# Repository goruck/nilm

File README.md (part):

# Energy Management Using Real-Time Non-Intrusive Load Monitoring

## Introduction

The goal of non-intrusive load monitoring (NILM) is to recover the energy consumption of individual appliances from the aggregate mains signal, which is a measure of the total electricity consumption of a building or house. NILM is also known as energy disaggregation and both terms will be used interchangeably throughout.

R. Gopinath, et al., nicely summarizes the rational behind NILM in the paper Energy management using non-intrusive load monitoring techniques — State- of-the-art and future research directions¹:

> In recent years, the development of smart sustainable cities has become the primary focus among urban planners and policy makers to make responsible use of resources, conserve the environment and improve the well-being of the society. Energy management is an integral part of the smart sustainable cities development programme which involves conscious and efficient use of available energy resources towards attaining sustainability and self-reliance on energy systems. Building sector is one of the key sectors that utilize more energy. Therefore, efforts are being made to monitor and manage energy consumption effectively in residential and commercial buildings. In recent years, non-intrusive load monitoring (NILM) technique has become a popular and emerging approach to monitor events (on/off) and energy consumption of appliances/electrical utilities in buildings using single energy meter. The information about the energy consumption at the appliance level would help consumers to understand their appliance usage behavior and take necessary steps for reducing energy consumption.

By using deep learning models trained on publicly available datasets it is now feasible to enable NILM in very cost effective ways by leveraging commodity hardware and open source software. Deploying the trained models at the edge of the power grid, i.e. the building level, results in additional cost savings since it obviates the need for always connected internet cloud services which can be expensive at scale and running the algorithms in real-time provides for low latency operation.

This Project will show you how NILM works by taking you through the steps I used to implement a prototype system at my house.

## Architecture

The following first two diagrams illustrate the NILM concept and process steps at a high level. The last diagram shows my prototype system which is based on these concepts and is implemented using Arduino- and Raspberry Pi-based compute.

")

")

## NILM Algorithm Selection and Models

### Algorithm Selection

Energy disaggregation is a highly underdetermined and a single-channel Blind Source Separation (BSS) problem² which makes it difficult to obtain accurate predictions. Let $M$ be the number of household appliances and $i$ be the index referring to the $i$-th appliance. The aggregate power consumption $x$ at a given time $t$ is the sum of the power consumption of all appliances $M$, denoted by $y_i\forall{i=1,...,M}$. Therefore, the total power consumption $x$ at a given time $t$ can expressed by the equation below.

$$
x(t)=\sum_{i=1}^{M} y_i(t) + \epsilon_{\text{noise}}(t)
$$

(1)

Where $\epsilon_{noise}$ is a noise term. The goal of this project is to solve the inverse problem and estimate the appliance power consumption $y_i$, given the aggregate power signal $x$, and to do so in a manner suitable for deployment at the edge. 

Past approaches have included factorial hidden Markov models (FHMM)¹ and various event-based methods with some success⁶. You can also solve the single-channel BSS problem can by using sequence-to-sequence (seq2seq) learning with neural networks, and it can applied to the NILM problem using transformers, convolutional and recurrent neural networks³. Seq2seq learning involves training a neural network to map between an input time series, such as the aggregate power readings the case of NILM, and a output sequence, such as the estimated energy consumption of a single appliance. A sliding input window is typically used to training the network which generates a corresponding window of the output. This method produces multiple predictions for each appliance in the output so an average of the predictions is used for the final result. Some of the predictions will be more accurate than others, especially those near the midpoint of the input sliding window. The averaging will tend to lower the overall accuracy of the predictions.

Some of the disadvantages of of seq2seq leaning can mitigated by sequence-to-point learning (seq2point) for single-channel BSS⁴. You also use a sliding input signal window in this approach, however the network is trained to predict the output signal only at the midpoint of the window which makes the prediction problem easier on the network, leading to more accurate results.

I selected the seq2point learning approach for my prototype system and my implementation was inspired and guided by work described by Michele D'Incecco, Stefano Squartini and Mingjun Zhong⁵. I developed a variety of seq2point learning models using Tensorflow as shown in the Python module [define_models.py](./ml/define_models.py) but focussed my work on the models `transformer` and `cnn`.

### Neural Network Models

The ```cnn``` model is depicted below for an input sequence length of 599 samples. The model generally follows traditional cnn concepts from vision use cases where several convolutional layers are used to extract features from the input power sequence at gradually finer details as the input traverses through the network. These features are the on-off patterns of the appliances as well as their power consumption levels. Max pooling is used to manage the complexity of the model after each convolutional layer. Finally, dense layers are used to output the final single point power consumption estimate for the window which is de-normalized before using in downstream processing. There are about 40 million parameters in this model using the default values.

The ```transformer``` model is depicted below for an input sequence length of 599 samples where the transformer block is a Bert-style encoder. The input sequence is first passed through a convolutional layer to expand it into a latent space which is analogous to the feature extraction in the cnn model case. These features are pooled and L2 normalized to reduce model complexity and to mitigate the effects of outliers. Next, the sequence features are processed by a Bert-style transformer lineup which includes positional embedding and transformer blocks that applies importance weighting. The output of the encoder is decoded by several layers which are comprised of relative position embedding which applies symmetric weights around the mid-point of the signal, average pooling which reduces the sequence to a single value per feature and then finally dense layers that output the final single point estimated power value for the window which again is de-normalized for downstream processing. There are about six million parameters in this model using the default values.

The Bert-style transformer encoder is depicted below.

## NILM Datasets

There are a number of large-scale publicly available datasets specifically designed to address the NILM problem which were captured in household buildings from various countries. The table⁷ below shows several of the most widely used.

")

The datasets generally include many 10’s of millions of active power, reactive power, current, and voltage samples but with different sampling frequencies which requires you to pre-process the data before use. Most NILM algorithms utilize only real (aka active or true) power data. Five appliances are usually considered for energy disaggregation research which are kettle, microwave, fridge, dish washer and washing machine. These are the appliances I considered for my prototype and following the work of Michele DIncecco, et al.⁵, I mainly focused on the REFIT⁸ dataset but will eventually include UK-DALE and REDD.

Note that these datasets are typically very imbalanced because the majority of the time an appliance is in the off state. 

## Model Training and Results

I used TensorFlow to train and test the model. All code associated with this section can be found on the Machine Learning section of the project’s GitHub, NILM⁹. The seq2point learning models for the appliances were trained individually on z-score standardized REFIT data or normalized to $[0, P_m]$, where $P_m$ is the maximum power consumption of an appliance in its active state. Using normalized data tended to give the best model performance so it is used by default.

I used the following metrics to evaluate the model’s performance. You can view the code that calculates these metrics [here](./ml/nilm_metric.py).

* Mean absolute error ($MAE$), which evaluates the absolute difference between the prediction and the ground truth power at every time point and calculates the mean value, as defined by the equation below.

$$
\mathrm{MAE}=\frac{1}{N}\sum_{i=1}^{N}\lvert \hat{x}_i - x_i\rvert
$$

(2)

* Normalized signal aggregate error ($SAE$), which indicates the relative error of the total energy. Denote $r$ as the total energy consumption of the appliance and $\hat{r}$ as the predicted total energy, then SAE is defined per the equation below.

$$
\mathrm{SAE}=\frac{\lvert \hat{r} - r\rvert}{r}
$$

(3)

* Energy per Day ($EpD$) which measures the predicted energy used in a day, useful when the household users are interested in the total energy consumed in a period. Denote $D$ as the total number of days and $e=\sum_{t}e_t$ as the appliance energy consumed in a day, then EpD is defined per the equation below.

$$
\mathrm{EpD}=\frac{1}{D}\sum_{n=1}^{D} e_n
$$

(4)

* Normalized disaggregation error ($NDE$) which measures the normalized error of the squared difference between the prediction and the ground truth power of the appliances, as defined by the equation below.

$$
\mathrm{NDE}=\frac{\sum_{i,t}\bigl(x_{i,t}-\hat{x}_{i,t}\bigr)^2}{\sum_{i,t} x_{i,t}^2}
$$

(5)

I also used accuracy ($ACC$), F1-score ($F1$) and Matthew’s correlation coefficient ($MCC$) to assess if the model can perform well with the severely imbalanced datasets used to train and test the model. These metrics depend on the on-off status of the device and are computed using the parameters in the [common.py](./ml/common.py) module. $ACC$ is equal to the number of correctly predicted time points over the test dataset. $F1$ and $MCC$ are computed according to the equations below where $TP$ stands for true positives, $TN$ stands for true negatives, $FP$ stands for false positives and $FN$ stands for false negatives.

$$
F_1=\frac{TP}{TP+\frac{1}{2}(FP+FN)}
$$

(6)

$$
\mathrm{MCC}=\frac{TN\cdot TP - FN\cdot FP}{\sqrt{(TP+FP)(TP+FN)(TN+FP)(TN+FN)}}
$$

(7)

$MAE$, $SAE$, $NDE$ and $EpD_e$ (defined as $ 100\% \times (EpD_{predicted} - EpD_{ground\_truth}) / EpD_{ground\_truth}$) reflect the model's ability to correctly predict the appliance energy consumption levels. $F1$ and $MCC$ indicates the model's ability to correctly predict appliance activations using imbalanced classes. $ACC$ is less useful in this application because most of the time the model will correctly predict the appliance is off which dominates the dataset.

A sliding window of 599 samples of the aggregate real power consumption signal is used as inputs to seq2point model and the midpoints of the corresponding windows of the appliances are used as targets. You can see how the samples and targets are generated by an instance of the WindowGenerator Class defined in the [window_generator.py](./ml/window_generator.py) module.

You can see the code I used to train the model in [train.py](./ml/train.py) which uses the `tf.distribute.MirroredStrategy()` distributed training strategy. I used the Keras Adam optimizer and to reduce over-fitting, early stopping is used. The training code can be configured to train the seq2point model from scratch, or given a fitted model, prune it or fine tune it with quantization aware training (QAT), both of which can improve inference performance especially on edge hardware.

The key hyper-parameters for training and the optimizer are summarized below.
* Input Window Size: 599 samples
* Global Batch size: 1024 samples.
* From scratch Learning Rate: 1e-04
* QAT and Prune Learning Rate: 1e-05
* Adam Optimizer: beta_1=0.9, beta_2=0.999, epsilon=1e-08.
* Early Stopping Criteria: 6 epochs.

The loss function<sup>11</sup> shown in the equation below is used to compute training gradients and to evaluate validation loss on a per-batch basis. It consists of a combination of Mean Squared Error, Binary Cross-Entropy and Mean Absolute Error losses, averaged over distributed model replica batches.

$$
L(x,s) = (\hat{x}-x)^{2}
        - [\hat{s}\log s + (1-\hat{s})\log(1-s)]
        + \lambda\,|\hat{x}-x|
$$

for $\hat{x} \in \mathcal{O}$.
(8)

Where $x, \hat{x}\in[0, 1]$ are the ground truth and predicted power usage single point values divided by the maximum power limit per appliance and $s, \hat{s}\in\set{0, 1}$ are the appliance state label and prediction, and $O$ is the set of predictions when either the status label is on or the prediction is incorrect. The hyperparameter $\lambda$ tunes the absolute loss term on an a per-appliance basis. 

You can find the training results for each appliance in the [models](./ml/models/) folder. Typical performance metrics for the `cnn` model are shown in the table below.

|Appliance|$F1\uparrow$|$MCC\uparrow$|$ACC\uparrow$|$MAE$ $(W)$ $\downarrow$|$SAE\downarrow$|$NDE\downarrow$|$EpD_e\thinspace(\%)\downarrow$|
| --- | --- | --- | --- | --- | --- | --- | --- |
|kettle|0.7309|0.7346|0.9960|8.788|0.2284|0.4696|-22.85|
|microwave|0.5671|0.5667|0.9933|7.564|0.0460|0.8845|-4.661|
|fridge|0.7929|0.6942|0.8645|12.33|0.0373|0.4111|3.733|
|dishwasher|0.6069|0.6483|0.9801|5.367|0.0347|0.3742|-3.473|
|washingmachine|0.8478|0.8441|0.9893|14.75|0.2929|0.3470|-29.29|

Typical performance metrics for the `transformer` model are shown in the table below.

|Appliance|$F1\uparrow$|$MCC\uparrow$|$ACC\uparrow$|$MAE$ $(W)$ $\downarrow$|$SAE\downarrow$|$NDE\downarrow$|$EpD_e\thinspace(\%)\downarrow$|
| --- | --- | --- | --- | --- | --- | --- | --- |
|kettle|0.8177|0.8176|0.9967|7.264|0.1348|0.3760|13.48|
|microwave|0.6530|0.6506|0.9952|6.428|0.1454|0.7496|-14.54|
|fridge|0.8138|0.7262|0.8799|11.02|0.0559|0.3743|5.590|
|dishwasher|0.6914|0.7119|0.9873|5.373|0.0690|0.3906|-6.904|
|washingmachine|0.8435|0.8420|0.9886|14.19|0.2440|0.2440|-24.40|

Average metrics across all appliances for both model architectures are compared in the table below.

|Architecture|$\overline{F1}\uparrow$|$\overline{MCC}\uparrow$|$\overline{ACC}\uparrow$|$\overline{MAE}$ $(W)$ $\downarrow$|$\overline{SAE}\downarrow$|$\overline{NDE}\downarrow$|$\overline{\|EpD_e\|}\thinspace(\%)\downarrow$|
| --- | --- | --- | --- | --- | --- | --- | --- |
|```cnn```|0.7161|0.7065|0.9643|9.852|0.1957|0.4528|19.57|
|```transformer```|0.7639|0.7497|0.9695|8.855|0.1298|0.3781|12.98|

You can see that the ```cnn``` and ```transformer``` models have similar performance even though the latter has about six times fewer parameters than the former. However, each ```transformer``` training step takes about seven times longer than ```cnn``` due to the `transformer` model's use of self-attention which has $O(n^2)$ complexity as compared to the `cnn` model's $O(n)$, where $n$ is the input sequence length. On the basis on training (and inference) efficiency, you can see that ```cnn``` is preferable with little loss in model performance.

You can find a variety of performance metrics in the literature to compare these results against, here are two examples. The middle column in the table<sup>5</sup> below shows another cnn-based model's performance. You can see the results of this project compare very favorably. 

The table<sup>12</sup> below shows the results from two transformer-based models (BERT4NILM and ELECTRIcity) and three other architectures. Although the data is incomplete, again this project's transformer-based model results compare favorably. 

## Model Quantization

I performed [Post-training quantization](https://www.tensorflow.org/lite/performance/post_training_quantization) on the ```cnn``` and ```transformer``` models using the [TensorFlow Lite converter API](https://www.tensorflow.org/lite/models/convert/) with various quantization modes to improve inference speed on edge hardware, including the Raspberry Pi and the Google Edge TPU, while mitigating the impact on accuracy. You can see the quantization modes I used in the table below.

|Mode|Description|
| --- | --- |
|convert_only|Convert to tflite but keep all parameters in Float32 (no quantization).|
|w8|Quantize weights from float32 to int8 and biases to int64. Leave activations in Float32.|
|w8_a8_fallback|Same as w8 but quantize activations from float32 to int8. Fallback to float if an operator does not have an integer implementation.|
|w8_a8|Same as w8 but quantize activations from float32 to int8. Enforce full int8 quantization for all operators.|
|w8_a16|Same as w8 but quantize activations to int16.|

The `cnn` model was quantized using all modes to understand the best tradeoff between latency and accuracy. Only the weights for the ```transformer``` model were quantized to int8 using mode `w8`, the activations needed to be kept in Float32 to maintain acceptable accuracy. See [convert_keras_to_tflite.py](./ml/convert_keras_to_tflite.py) for the code that does this quantization which also uses [TensorFlow Lite's quantization debugger](https://www.tensorflow.org/lite/performance/quantization_debugger) to check how well each layer in the model was quantized. I also profiled the converted models using the [TensorFlow Lite Model Benchmark Tool](https://github.com/tensorflow/tensorflow/tree/master/tensorflow/lite/tools/benchmark) to quantify inference latencies.

The quantized inference results are shown in the tables below, where $L_{x86}$ is the average inference latency on a 3.8 GHz x86 machine using eight tflite interpreter threads and $L_{arm}$ is the average inference latency on the ARM aarch-64-based Raspberry Pi 4 using four threads with both computers using the TensorFlow Lite [XNNPACK](https://github.com/google/XNNPACK) CPU delegate. $L_{tpu}$ is the average inference latency on the Google Coral Edge TPU. Model inputs and outputs were keep in float32 to maximize inference speed for the x86- and ARM-based machines but were set to int8 for the edge tpu.

### CNN Model Results and Discussion

The quantized results for the ```cnn``` models are shown in the table below for quantization mode ```w8```.

|Appliance|$F1\uparrow$|$MCC\uparrow$|$ACC\uparrow$|$MAE$ $(W)$ $\downarrow$|$SAE\downarrow$|$NDE\downarrow$|$EpD_e$ ($\%$)|$L_{x86}$ (${\mu}s$)|$L_{arm}$ (${\mu}s$)|
| --- | --- | --- | --- | --- | --- | --- | --- | --- | --- |
|kettle|0.7428|0.7454|0.9966|7.371|0.2013|0.4500|-20.13|743.910|3809.41|
|microwave|0.6400|0.6373|0.9933|7.971|0.1578|0.7194|-15.78|736.549|3586.55|
|fridge|0.6491|0.5040|0.7935|17.78|0.0907|0.7000|-8.971|731.371|3520.54|
|dishwasher|0.5143|0.5787|0.9719|5.3955|0.0569|0.3647|-5.694|742.279|3519.52|
|washingmachine|0.8838|0.8791|0.9919|15.33|0.2930|0.3811|-29.30|751.801|3515.68|

The quantized results for the ```cnn kettle``` model are shown below for the other quantization modes.

|Mode|$F1\uparrow$|$MCC\uparrow$|$ACC\uparrow$|$MAE$ $(W)$ $\downarrow$|$SAE\downarrow$|$NDE\downarrow$|$EpD_e$ ($\%$)|$L_{x86}$ (${\mu}s$)|$L_{arm}$ (${\mu}s$)|$L_{tpu}$ (${\mu}s$)|
| --- | --- | --- | --- | --- | --- | --- | --- | --- | --- | --- |
|convert_only|0.7119|0.7199|0.9964|7.812|0.2862|0.4780|-28.65|309.531|12890.10|NA|
|w8_a8_fallback|0.6584|0.6736|0.9959|8.677|0.3700|0.5448|-36.70|186.483|3435.56|NA|
|w8_a8|0.6584|0.6736|0.9960|8.768|0.3670|0.5447|-36.70|185.403|3258.19|27777.8|
|w8_a16|0.7474|0.7479|0.9966|7.431|0.1531|0.4516|-15.31|5095.38|24065.3|NA|

The quantized results for the ```cnn microwave``` model are shown below for the other quantization modes.

|Mode|$F1\uparrow$|$MCC\uparrow$|$ACC\uparrow$|$MAE$ $(W)$ $\downarrow$|$SAE\downarrow$|$NDE\downarrow$|$EpD_e$ ($\%$)|$L_{x86}$ (${\mu}s$)|$L_{arm}$ (${\mu}s$)|$L_{tpu}$ (${\mu}s$)|
| --- | --- | --- | --- | --- | --- | --- | --- | --- | --- | --- |
|convert_only|0.6410|0.6384|0.9933|7.976|0.1630|0.7195|-18.30|302.750|13055.3|NA|
|w8_a8_fallback|0.6268|0.6238|0.9931|8.006|0.1796|0.7206|-17.96|187.232|3458.30|NA|
|w8_a8|0.6268|0.6238|0.9931|8.005|0.1796|0.7206|-17.96|183.910|3466.65|100000|
|w8_a16|0.6391|0.6365|0.9933|7.968|0.1590|0.7172|-15.89|5100.76|24052.0|NA|

Results for the other appliance models are omitted for brevity but show similar characteristics as a function of quantization mode.

You can see the negative impact of activation quantization but weight quantization, because of regularization effects, has a moderate benefit on some model performance metrics. As expected, the full quantization modes lead to the lowest latencies. Quantizing activations to int16 by the ```w8_a16``` mode results in the highest latencies because only non-optimized reference kernel implementations are presently available in TensorFlow Lite but this scheme leads to the best model metrics given the regularization benefits from weight quantization and better preservation of activation numerics.

You can also see that inference latency of the modes follows ```w8``` ${>}$ ```convert_only``` ${>}$ ```w8_a8``` for the x86 machine but ```convert_only``` ${>}$ ```w8``` ${>}$ ```w8_a8``` for the aarch64 machine, although the variation is larger for x86. To better understand this, I profiled the converted models using the [TFLite Model Benchmark Tool](https://github.com/tensorflow/tensorflow/tree/master/tensorflow/lite/tools/benchmark). A summary of the profiling results for the ```cnn microwave``` model are shown below which are representative of the other models.

#### Model Profiling on x86 (slowest to fastest)
You can see that the Fully Connected and Convolution operations are taking the longest to execute in all cases but are much faster in the fully quantized mode of ```w8_a8```.

| w8 node type                     | count | avg_ms | avg %    | cdf %    | mem KB | times called |
| ----------------------------- | ----- | ------ | -------- | -------- | ------ | ------------ |
| FULLY_CONNECTED               | 2     | 0.397  | 56.5527% | 56.5527% | 0      | 2            |
| CONV_2D                       | 4     | 0.204  | 29.0598% | 85.6125% | 0      | 4            |
| Copy (NC X32)                 | 2     | 0.051  | 7.26496% | 92.8775% | 0      | 9            |
| Max Pooling (NHWC F32)        | 1     | 0.038  | 5.41311% | 98.2906% | 0      | 4            |
| Convolution (NHWC F32) IGEMM  | 1     | 0.012  | 1.7094%  | 100%     | 0      | 1            |
| Fully Connected (NC F32) GEMM | 1     | 0      | 0%       | 100%     | 0      | 1            |
| EXPAND_DIMS                   | 9     | 0      | 0%       | 100%     | 0      | 9            |

| convert_only node type        | count | avg_ms | avg %    | cdf %    | mem KB | times called |
| ----------------------------- | ----- | ------ | -------- | -------- | ------ | ------------ |
| Fully Connected (NC F32) GEMM | 3     | 0.151  | 53.3569% | 53.3569% | 0      | 3            |
| Convolution (NHWC F32) IGEMM  | 1     | 0.062  | 21.9081% | 75.265%  | 0      | 5            |
| Max Pooling (NHWC F32)        | 1     | 0.037  | 13.0742% | 88.3392% | 0      | 4            |
| Copy (NC X32)                 | 1     | 0.033  | 11.6608% | 100%     | 0      | 9            |
| EXPAND_DIMS                   | 9     | 0      | 0%       | 100%     | 0      | 9            |

| w8_a8 node type                     | count | avg_ms | avg %    | cdf %    | mem KB | times called |
| ----------------------------- | ----- | ------ | -------- | -------- | ------ | ------------ |
| Convolution (NHWC QC8) IGEMM  | 1     | 0.061  | 37.1951% | 37.1951% | 0      | 5            |
| Fully Connected (NC QS8) GEMM | 3     | 0.037  | 22.561%  | 59.7561% | 0      | 3            |
| Max Pooling (NHWC S8)         | 1     | 0.034  | 20.7317% | 80.4878% | 0      | 4            |
| Copy (NC X8)                  | 1     | 0.032  | 19.5122% | 100%     | 0      | 9            |
| EXPAND_DIMS                   | 9     | 0      | 0%       | 100%     | 0      | 9            |
| Convert (NC QS8 F32)          | 1     | 0      | 0%       | 100%     | 0      | 1            |
| Convert (NC F32 QS8)          | 1     | 0      | 0%       | 100%     | 0      | 1            |

#### Model Profiling on aarch64 (slowest to fastest)
You can see the copy and Max Pooling operations in particular are relatively slower on x86 than on aarch64 which is probably due to memory bandwidth and micro-architecture differences.

| convert_only node type | count | avg_ms | avg %       | cdf %    | mem KB | times called |
| ------------------------------ | ----- | ------ | ----------- | -------- | ------ | ------------ |
| Copy (NC X32)                  | 1     | 34.835 | 30.9136%    | 30.9136% | 0      | 9            |
| Convolution (NHWC F32) IGEMM   | 1     | 32.414 | 28.7651%    | 59.6787% | 0      | 5            |
| Max Pooling (NHWC F32)         | 1     | 23.008 | 20.418%     | 80.0967% | 0      | 4            |
| Fully Connected (NC F32) GEMM  | 3     | 22.425 | 19.9006%    | 99.9973% | 0      | 3            |
| EXPAND_DIMS                    | 9     | 0.003  | 0.00266229% | 100%     | 0      | 9            |

| w8 node type                     | count | avg_ms | avg %       | cdf %    | mem KB | times called |
| ----------------------------- | ----- | ------ | ----------- | -------- | ------ | ------------ |
| Max Pooling (NHWC F32)        | 1     | 42.281 | 46.9085%    | 46.9085% | 0      | 4            |
| CONV_2D                       | 4     | 17.461 | 19.3721%    | 66.2806% | 0      | 4            |
| Copy (NC X32)                 | 2     | 16.877 | 18.7241%    | 85.0047% | 0      | 9            |
| Convolution (NHWC F32) IGEMM  | 1     | 10.658 | 11.8245%    | 96.8292% | 0      | 1            |
| FULLY_CONNECTED               | 2     | 2.847  | 3.1586%     | 99.9878% | 0      | 2            |
| Fully Connected (NC F32) GEMM | 1     | 0.007  | 0.00776613% | 99.9956% | 0      | 1            |
| EXPAND_DIMS                   | 9     | 0.004  | 0.00443779% | 100%     | 0      | 9            |

| w8_a8 node type                     | count | avg_ms | avg %        | cdf %    | mem KB | times called |
| ----------------------------- | ----- | ------ | ------------ | -------- | ------ | ------------ |
| Copy (NC X8)                  | 1     | 34.686 | 30.9647%     | 30.9647% | 0      | 9            |
| Convolution (NHWC QC8) IGEMM  | 1     | 33.259 | 29.6908%     | 60.6554% | 0      | 5            |
| Max Pooling (NHWC S8)         | 1     | 23.922 | 21.3555%     | 82.0109% | 0      | 4            |
| Fully Connected (NC QS8) GEMM | 3     | 20.146 | 17.9846%     | 99.9955% | 0      | 3            |
| EXPAND_DIMS                   | 9     | 0.002  | 0.00178543%  | 99.9973% | 0      | 9            |
| Convert (NC F32 QS8)          | 1     | 0.002  | 0.00178543%  | 99.9991% | 0      | 1            |
| Convert (NC QS8 F32)          | 1     | 0.001  | 0.000892714% | 100%     | 0      | 1            |

#### Quantization Efficacy

The RMSE / scale is close to $1 / sqrt(12)$ (~ 0.289) when quantized distribution is similar to the original float distribution, indicating a well-quantized model. The larger the value is, it's more likely for the layer not being quantized well. The tables below show the RMSE / Scale metric for the ```cnn kettle``` and ```cnn washingmachine``` models and the `Suspected?` column indicates a layer that significantly exceeds 0.289. Other models are omitted for brevity but show similar results. These layers can remain in float to generate a selectively quantized model that increases accuracy at the expense of inference performance but doing so for the ```cnn``` models did not materially improve accuracy. See [Inspecting Quantization Errors with Quantization Debugger](https://www.tensorflow.org/lite/performance/quantization_debugger).

Layer quantization efficacy metrics for the `cnn kettle` model using mode `w8_a8` are shown below.

| layer | op_name | range | rmse/scale | Suspected? |
| ------ | --------------- | --------- | ---------- | --- |
| 0      | EXPAND_DIMS     | 23.929975 | 2.75E-01   |
| 1      | CONV_2D         | 5.518012  | 2.22E-01   |
| 2      | RESHAPE         | 5.518012  | 2.38E-06   |
| 3      | EXPAND_DIMS     | 5.518012  | 2.38E-06   |
| 4      | MAX_POOL_2D     | 5.518012  | 2.42E-06   |
| 5      | RESHAPE         | 5.518012  | 2.42E-06   |
| 6      | EXPAND_DIMS     | 5.518012  | 2.42E-06   |
| 7      | CONV_2D         | 3.494575  | 1.79E-01   |
| 8      | RESHAPE         | 3.494575  | 1.44E-06   |
| 9      | EXPAND_DIMS     | 3.494575  | 1.44E-06   |
| 10     | MAX_POOL_2D     | 3.494575  | 1.49E-06   |
| 11     | RESHAPE         | 3.494575  | 1.49E-06   |
| 12     | EXPAND_DIMS     | 3.494575  | 1.49E-06   |
| 13     | CONV_2D         | 5.910911  | 1.22E-01   |
| 14     | RESHAPE         | 5.910911  | 1.09E-06   |
| 15     | EXPAND_DIMS     | 5.910911  | 1.09E-06   |
| 16     | MAX_POOL_2D     | 5.910911  | 1.18E-06   |
| 17     | RESHAPE         | 5.910911  | 1.18E-06   |
| 18     | EXPAND_DIMS     | 5.910911  | 1.18E-06   |
| 19     | CONV_2D         | 10.82671  | 1.00E-01   |
| 20     | RESHAPE         | 10.82671  | 1.00E-06   |
| 21     | EXPAND_DIMS     | 10.82671  | 1.00E-06   |
| 22     | MAX_POOL_2D     | 10.82671  | 1.08E-06   |
| 23     | RESHAPE         | 10.82671  | 1.08E-06   |
| 24     | EXPAND_DIMS     | 10.82671  | 1.08E-06   |
| 25     | CONV_2D         | 2.987664  | 5.77E-02   |
| 26     | RESHAPE         | 2.987664  | 3.82E-07   |
| 27     | FULLY_CONNECTED | 1.725032  | 1.20E+00   | Yes |
| 28     | FULLY_CONNECTED | 1.512342  | 6.19E-01   |
| 29     | FULLY_CONNECTED | 0.990833  | 2.03E+00   | Yes |

Layer quantization efficacy metrics for the `cnn washingmachine` model using mode `w8_a8` are shown below.

| layer | op_name | range | rmse/scale | Suspected? |
| ------- | --------------- | ---------- | -------- | --- |
| 0       | EXPAND_DIMS     | 30.954547  | 3.00E-01 |
| 1       | CONV_2D         | 12.620701  | 1.81E-01 |
| 2       | RESHAPE         | 12.620701  | 1.56E-06 |
| 3       | EXPAND_DIMS     | 12.620701  | 1.56E-06 |
| 4       | MAX_POOL_2D     | 12.620701  | 1.67E-06 |
| 5       | RESHAPE         | 12.620701  | 1.67E-06 |
| 6       | EXPAND_DIMS     | 12.620701  | 1.67E-06 |
| 7       | CONV_2D         | 15.030776  | 1.94E-01 |
| 8       | RESHAPE         | 15.030776  | 1.94E-07 |
| 9       | EXPAND_DIMS     | 15.030776  | 1.94E-07 |
| 10      | MAX_POOL_2D     | 15.030776  | 2.36E-07 |
| 11      | RESHAPE         | 15.030776  | 2.36E-07 |
| 12      | EXPAND_DIMS     | 15.030776  | 2.36E-07 |
| 13      | CONV_2D         | 10.132236  | 1.68E-01 |
| 14      | RESHAPE         | 10.132236  | 1.83E-06 |
| 15      | EXPAND_DIMS     | 10.132236  | 1.83E-06 |
| 16      | MAX_POOL_2D     | 10.132236  | 2.06E-06 |
| 17      | RESHAPE         | 10.132236  | 2.06E-06 |
| 18      | EXPAND_DIMS     | 10.132236  | 2.06E-06 |
| 19      | CONV_2D         | 9.038437   | 1.45E-01 |
| 20      | RESHAPE         | 9.038437   | 1.90E-06 |
| 21      | EXPAND_DIMS     | 9.038437   | 1.90E-06 |
| 22      | MAX_POOL_2D     | 9.038437   | 2.20E-06 |
| 23      | RESHAPE         | 9.038437   | 2.20E-06 |
| 24      | EXPAND_DIMS     | 9.038437   | 2.20E-06 |
| 25      | CONV_2D         | 5.151932   | 9.58E-02 |
| 26      | RESHAPE         | 5.151932   | 1.08E-06 |
| 27      | FULLY_CONNECTED | 7.269378   | 1.13E-01 |
| 28      | FULLY_CONNECTED | 3.79172    | 1.75E-01 |
| 29      | FULLY_CONNECTED | 1.102378   | 9.51E-01 | Yes |

#### Model Memory Footprint

I used the [TFLite Model Benchmark Tool](https://github.com/tensorflow/tensorflow/tree/master/tensorflow/lite/tools/benchmark) to get the approximate RAM consumption of the TFLite ```cnn microwave``` model at runtime which is shown in the table below for each quantization mode as well as the TFLite model disk space. The other `cnn` models show similar characteristics. The findings for the x86 architecture were identical to the arm architecture. Note that the Keras model consumes about 42.49 (MB) on disk. You can see that there is about a four times reduction in disk storage space due to the float32 to int8 weight conversions. Interestingly, RAM runtime usage varies considerably due to the TFLite algorithms that that optimize intermediate tensors usage. These are pre-allocated to reduce inference latency at the cost of memory space. See [Optimizing TensorFlow Lite Runtime Memory](https://blog.tensorflow.org/2020/10/optimizing-tensorflow-lite-runtime.html).

| Quant Mode | Disk (MB) | RAM (MB) |
| --- | --- | --- |
| convert_only | 42.485044 | 84.957 |
| w8 | 10.642040 | 12.7109 |
| w8_a8 | 10.648016 | 23.3633 |
| w8_a16 | 10.660984 | 10.1836 |

### Transformer Model Results and Discussion

Note that even though the XNNPACK delagate was enabled during `transformer` model inference evaluation nothing was actually accelerated because the `transformer` model contains dynamic tensors. The following warning is shown when using the TFLite interpreter for inference:

`Attempting to use a delegate that only supports static-sized tensors with a graph that has dynamic-sized tensors (tensor#94 is a dynamic-sized tensor).`

This means that all operators are unsupported by XNNPACK and will fall back to the default CPU kernel implementations. A future effort will involve refactoring the `transformer` model use only static-size tensors. Note that a tensor could be marked dynamic at TFLite runtime when there is a control-flow operation (e.g., `if`, `while` etc.) prepared. In other words, even when the model graph itself doesn't have any tensors of dynamic shapes statically, at runtime a model could have dynamic tensors. The current transformer model uses `if` control-flow operations.

The quantized results for the ```transformer``` model are shown in the table below for quantization mode ```w8```.

|Appliance|$F1\uparrow$|$MCC\uparrow$|$ACC\uparrow$|$MAE$ $(W)$ $\downarrow$|$SAE\downarrow$|$NDE\downarrow$|$EpD_e$ ($\%$)|$L_{x86}$ (${\mu}s$)|$L_{arm}$ (${\mu}s$)|
| --- | --- | --- | --- | --- | --- | --- | --- | --- | --- |
|kettle|0.8460|0.8483|0.9977|5.117|0.1761|0.2760|-17.61|20520|61939|
|microwave|0.7375|0.7355|0.9952|6.969|0.3435|0.6049|-34.35|20905|60823|
|fridge|0.7437|0.6261|0.8381|14.52|0.0838|0.5518|-8.560|20986|61862|
|dishwasher|0.6671|0.6905|0.9860|6.214|0.1117|0.4521|-11.17|20983|63432|
|washingmachine|0.8910|0.8872|0.9926|15.08|0.3796|0.3442|-37.96|21426|60901|

The quantized results for the ```transformer``` `kettle` and `microwave` models are shown in the table below for quantization mode ```convert_only```.

|Appliance|$F1\uparrow$|$MCC\uparrow$|$ACC\uparrow$|$MAE$ $(W)$ $\downarrow$|$SAE\downarrow$|$NDE\downarrow$|$EpD_e$ ($\%$)|$L_{x86}$ (${\mu}s$)|$L_{arm}$ (${\mu}s$)|
| --- | --- | --- | --- | --- | --- | --- | --- | --- | --- |
|kettle|0.8460|0.8483|0.9977|5.117|0.1761|0.2760|-17.61|7100|69746|
|microwave|0.6719|0.6736|0.9948|7.054|0.3930|0.6518|-39.30|7050|68667|

#### Model Profiling on x86 (slowest to fastest)

| w8 node type          | count | avg_ms | avg %      | cdf %    | mem KB | times called |
| ------------------ | ----- | ------ | ---------- | -------- | ------ | ------------ |
| FULLY_CONNECTED    | 14    | 16.243 | 79.5485%   | 79.5485% | 0      | 14           |
| ADD                | 41    | 0.667  | 3.26657%   | 82.815%  | 0      | 41           |
| MUL                | 42    | 0.661  | 3.23718%   | 86.0522% | 0      | 42           |
| BATCH_MATMUL       | 4     | 0.582  | 2.85029%   | 88.9025% | 0      | 4            |
| TRANSPOSE          | 20    | 0.551  | 2.69847%   | 91.601%  | 0      | 20           |
| RESHAPE            | 48    | 0.384  | 1.8806%    | 93.4816% | 0      | 48           |
| POW                | 2     | 0.371  | 1.81694%   | 95.2985% | 0      | 2            |
| SOFTMAX            | 2     | 0.202  | 0.989275%  | 96.2878% | 0      | 2            |
| MEAN               | 13    | 0.177  | 0.86684%   | 97.1546% | 0      | 13           |
| CONV_2D            | 1     | 0.152  | 0.744405%  | 97.899%  | 0      | 1            |
| SQUARED_DIFFERENCE | 6     | 0.119  | 0.582791%  | 98.4818% | 0      | 6            |
| TANH               | 2     | 0.11   | 0.538714%  | 99.0205% | 0      | 2            |
| AVERAGE_POOL_2D    | 1     | 0.086  | 0.421176%  | 99.4417% | 0      | 1            |
| FILL               | 14    | 0.059  | 0.288947%  | 99.7306% | 0      | 14           |
| SQUARE             | 1     | 0.036  | 0.176306%  | 99.9069% | 0      | 1            |
| SQRT               | 1     | 0.019  | 0.0930506% | 100%     | 0      | 1            |
| SUB                | 6     | 0      | 0%         | 100%     | 0      | 6            |
| STRIDED_SLICE      | 14    | 0      | 0%         | 100%     | 0      | 14           |
| SHAPE              | 24    | 0      | 0%         | 100%     | 0      | 24           |
| RSQRT              | 6     | 0      | 0%         | 100%     | 0      | 6            |
| REDUCE_PROD        | 16    | 0      | 0%         | 100%     | 0      | 16           |
| PACK               | 22    | 0      | 0%         | 100%     | 0      | 22           |
| GATHER             | 16    | 0      | 0%         | 100%     | 0      | 16           |
| EXPAND_DIMS        | 2     | 0      | 0%         | 100%     | 0      | 2            |
| CONCATENATION      | 8     | 0      | 0%         | 100%     | 0      | 8            |

| convert_only node type          | count | avg_ms | avg %     | cdf %    | mem KB | times called |
| ------------------ | ----- | ------ | --------- | -------- | ------ | ------------ |
| FULLY_CONNECTED    | 14    | 2.211  | 31.0447%  | 31.0447% | 0      | 14           |
| ADD                | 41    | 1.344  | 18.8711%  | 49.9158% | 0      | 41           |
| MUL                | 42    | 0.693  | 9.73041%  | 59.6462% | 0      | 42           |
| RESHAPE            | 48    | 0.619  | 8.69138%  | 68.3375% | 0      | 48           |
| BATCH_MATMUL       | 4     | 0.529  | 7.42769%  | 75.7652% | 0      | 4            |
| TRANSPOSE          | 20    | 0.4    | 5.6164%   | 81.3816% | 0      | 20           |
| POW                | 2     | 0.394  | 5.53215%  | 86.9138% | 0      | 2            |
| MEAN               | 13    | 0.216  | 3.03286%  | 89.9466% | 0      | 13           |
| SOFTMAX            | 2     | 0.155  | 2.17636%  | 92.123%  | 0      | 2            |
| SQUARED_DIFFERENCE | 6     | 0.128  | 1.79725%  | 93.9202% | 0      | 6            |
| TANH               | 2     | 0.119  | 1.67088%  | 95.5911% | 0      | 2            |
| AVERAGE_POOL_2D    | 1     | 0.102  | 1.43218%  | 97.0233% | 0      | 1            |
| FILL               | 14    | 0.099  | 1.39006%  | 98.4134% | 0      | 14           |
| CONV_2D            | 1     | 0.051  | 0.716091% | 99.1294% | 0      | 1            |
| SQUARE             | 1     | 0.037  | 0.519517% | 99.649%  | 0      | 1            |
| SQRT               | 1     | 0.025  | 0.351025% | 100%     | 0      | 1            |
| SUB                | 6     | 0      | 0%        | 100%     | 0      | 6            |
| STRIDED_SLICE      | 14    | 0      | 0%        | 100%     | 0      | 14           |
| SHAPE              | 24    | 0      | 0%        | 100%     | 0      | 24           |
| RSQRT              | 6     | 0      | 0%        | 100%     | 0      | 6            |
| REDUCE_PROD        | 16    | 0      | 0%        | 100%     | 0      | 16           |
| PACK               | 22    | 0      | 0%        | 100%     | 0      | 22           |
| GATHER             | 16    | 0      | 0%        | 100%     | 0      | 16           |
| EXPAND_DIMS        | 2     | 0      | 0%        | 100%     | 0      | 2            |
| CONCATENATION      | 8     | 0      | 0%        | 100%     | 0      | 8            |

#### Model Profiling on aarch64 (slowest to fastest)

| convert_only node type | count | avg_ms | avg %       | cdf %    | mem KB | times called |
| ---------------------- | ----- | ------ | ----------- | -------- | ------ | ------------ |
| FULLY_CONNECTED        | 14    | 30.777 | 44.8716%    | 44.8716% | 0      | 14           |
| MUL                    | 42    | 8.571  | 12.4962%    | 57.3678% | 0      | 42           |
| ADD                    | 41    | 7.425  | 10.8254%    | 68.1931% | 0      | 41           |
| POW                    | 2     | 5.308  | 7.73885%    | 75.932%  | 0      | 2            |
| BATCH_MATMUL           | 4     | 3.82   | 5.56941%    | 81.5014% | 0      | 4            |
| TRANSPOSE              | 20    | 3.352  | 4.88708%    | 86.3885% | 0      | 20           |
| RESHAPE                | 48    | 2.927  | 4.26745%    | 90.6559% | 0      | 48           |
| TANH                   | 2     | 2.02   | 2.94508%    | 93.601%  | 0      | 2            |
| SOFTMAX                | 2     | 1.182  | 1.72331%    | 95.3243% | 0      | 2            |
| MEAN                   | 13    | 0.927  | 1.35153%    | 96.6758% | 0      | 13           |
| SQUARED_DIFFERENCE     | 6     | 0.761  | 1.10951%    | 97.7854% | 0      | 6            |
| AVERAGE_POOL_2D        | 1     | 0.517  | 0.753765%   | 98.5391% | 0      | 1            |
| SQUARE                 | 1     | 0.326  | 0.475295%   | 99.0144% | 0      | 1            |
| CONV_2D                | 1     | 0.281  | 0.409687%   | 99.4241% | 0      | 1            |
| SQRT                   | 1     | 0.148  | 0.215778%   | 99.6399% | 0      | 1            |
| PACK                   | 22    | 0.105  | 0.153086%   | 99.793%  | 0      | 22           |
| FILL                   | 14    | 0.077  | 0.112263%   | 99.9052% | 0      | 14           |
| SUB                    | 6     | 0.022  | 0.0320751%  | 99.9373% | 0      | 6            |
| RSQRT                  | 6     | 0.022  | 0.0320751%  | 99.9694% | 0      | 6            |
| STRIDED_SLICE          | 14    | 0.012  | 0.0174955%  | 99.9869% | 0      | 14           |
| SHAPE                  | 24    | 0.005  | 0.0072898%  | 99.9942% | 0      | 24           |
| EXPAND_DIMS            | 2     | 0.003  | 0.00437388% | 99.9985% | 0      | 2            |
| CONCATENATION          | 8     | 0.001  | 0.00145796% | 100%     | 0      | 8            |
| REDUCE_PROD            | 16    | 0      | 0%          | 100%     | 0      | 16           |
| GATHER                 | 16    | 0      | 0%          | 100%     | 0      | 16           |

| w8 node type       | count | avg_ms | avg %       | cdf %    | mem KB | times called |
| ------------------ | ----- | ------ | ----------- | -------- | ------ | ------------ |
| FULLY_CONNECTED    | 14    | 22.759 | 38.6283%    | 38.6283% | 0      | 14           |
| MUL                | 42    | 7.718  | 13.0996%    | 51.7278% | 0      | 42           |
| ADD                | 41    | 6.952  | 11.7994%    | 63.5273% | 0      | 41           |
| POW                | 2     | 5.074  | 8.61197%    | 72.1392% | 0      | 2            |
| BATCH_MATMUL       | 4     | 3.773  | 6.40382%    | 78.5431% | 0      | 4            |
| TRANSPOSE          | 20    | 2.982  | 5.06127%    | 83.6043% | 0      | 20           |
| RESHAPE            | 48    | 2.902  | 4.92549%    | 88.5298% | 0      | 48           |
| TANH               | 2     | 1.95   | 3.30968%    | 91.8395% | 0      | 2            |
| SOFTMAX            | 2     | 1.222  | 2.07407%    | 93.9136% | 0      | 2            |
| MEAN               | 13    | 0.91   | 1.54452%    | 95.4581% | 0      | 13           |
| SQUARED_DIFFERENCE | 6     | 0.79   | 1.34085%    | 96.7989% | 0      | 6            |
| CONV_2D            | 1     | 0.659  | 1.1185%     | 97.9174% | 0      | 1            |
| AVERAGE_POOL_2D    | 1     | 0.48   | 0.814692%   | 98.7321% | 0      | 1            |
| SQUARE             | 1     | 0.359  | 0.609321%   | 99.3414% | 0      | 1            |
| SQRT               | 1     | 0.126  | 0.213857%   | 99.5553% | 0      | 1            |
| PACK               | 22    | 0.107  | 0.181608%   | 99.7369% | 0      | 22           |
| FILL               | 14    | 0.082  | 0.139176%   | 99.8761% | 0      | 14           |
| SUB                | 6     | 0.025  | 0.0424319%  | 99.9185% | 0      | 6            |
| RSQRT              | 6     | 0.023  | 0.0390373%  | 99.9576% | 0      | 6            |
| STRIDED_SLICE      | 14    | 0.013  | 0.0220646%  | 99.9796% | 0      | 14           |
| EXPAND_DIMS        | 2     | 0.005  | 0.00848637% | 99.9881% | 0      | 2            |
| SHAPE              | 24    | 0.004  | 0.0067891%  | 99.9949% | 0      | 24           |
| GATHER             | 16    | 0.002  | 0.00339455% | 99.9983% | 0      | 16           |
| CONCATENATION      | 8     | 0.001  | 0.00169727% | 100%     | 0      | 8            |
| REDUCE_PROD        | 16    | 0      | 0%          | 100%     | 0      | 16           |

#### Quantization Efficacy

Layer quantization efficacy metrics for the `transformer kettle` model using mode `w8_a8` are shown in the table below, although as noted above quantizing the transformer model's activations results in very poor model performance. You can see the `RSQRT` operator in particular does not quantize well, these operators are used in the Gaussian error linear activation functions which helps explain the poor performance of the model. The other `transformer `appliance models show similar efficacy metrics.

| layer | op_name            | range       | rmse/scale   | Suspect? |
| --- | ------------------ | ----------- | ------------ | -------- |
| 0   | EXPAND_DIMS        | 23.929975   | 0.2751951    |          |
| 1   | CONV_2D            | 6.793423    | 0.2952648    |          |
| 2   | RESHAPE            | 12.080546   | 0.1608947    |          |
| 3   | EXPAND_DIMS        | 12.080546   | 0            |          |
| 4   | AVERAGE_POOL_2D    | 12.080546   | 0            |          |
| 5   | ADD                | 11.598116   | 0.03801457   |          |
| 6   | RESHAPE            | 3.405601    | 0.0580239    |          |
| 7   | FILL               | 1           | 0            |          |
| 8   | MUL                | 0.489979    | 0.2888043    |          |
| 9   | ADD                | 3.72709     | 0.2890081    |          |
| 10  | FILL               | 1           | 0            |          |
| 11  | FILL               | 2E-06       | 0            |          |
| 12  | RESHAPE            | 3.72709     | 0            |          |
| 13  | TRANSPOSE          | 3.72709     | 0            |          |
| 14  | MEAN               | 1.371433    | 0.3178885    |          |
| 15  | SQUARED_DIFFERENCE | 4.45292     | 0.2296307    |          |
| 16  | MEAN               | 0.547054    | 0.2962779    |          |
| 17  | ADD                | 0.548054    | 0.4589049    |          |
| 18  | RSQRT              | 15.745848   | 41.5733      | Yes |
| 19  | MUL                | 15.745848   | 0            |          |
| 20  | MUL                | 9.606549    | 0.3037147    |          |
| 21  | MUL                | 2.384117    | 0.2467738    |          |
| 22  | SUB                | 2.384117    | 1.428423E-06 |          |
| 23  | ADD                | 8.792654    | 0.3326802    |          |
| 24  | TRANSPOSE          | 8.792654    | 0            |          |
| 25  | RESHAPE            | 8.792654    | 0            |          |
| 26  | MUL                | 8.606096    | 0.2844383    |          |
| 27  | ADD                | 8.682471    | 0.2893911    |          |
| 28  | RESHAPE            | 8.682471    | 0            |          |
| 29  | FULLY_CONNECTED    | 13.589397   | 0.337322     |          |
| 30  | RESHAPE            | 13.589397   | 0            |          |
| 31  | ADD                | 13.66659    | 0.2940356    |          |
| 32  | RESHAPE            | 13.66659    | 0            |          |
| 33  | TRANSPOSE          | 13.66659    | 0            |          |
| 34  | FULLY_CONNECTED    | 16.061866   | 0.3192651    |          |
| 35  | RESHAPE            | 16.061866   | 0            |          |
| 36  | ADD                | 16.14824    | 0.2843503    |          |
| 37  | RESHAPE            | 16.14824    | 0            |          |
| 38  | TRANSPOSE          | 16.14824    | 0            |          |
| 39  | BATCH_MATMUL       | 791.061     | 0.2887679    |          |
| 40  | MUL                | 69.920572   | 1.274111E-06 |          |
| 41  | SOFTMAX            | 0.996094    | 0.1901133    |          |
| 42  | FULLY_CONNECTED    | 15.370091   | 0.3185204    |          |
| 43  | RESHAPE            | 15.370091   | 0            |          |
| 44  | ADD                | 15.420575   | 0.273666     |          |
| 45  | RESHAPE            | 15.420575   | 0            |          |
| 46  | TRANSPOSE          | 15.420575   | 0            |          |
| 47  | BATCH_MATMUL       | 13.788238   | 0.2886845    |          |
| 48  | TRANSPOSE          | 13.788238   | 0            |          |
| 49  | RESHAPE            | 13.788238   | 0            |          |
| 50  | RESHAPE            | 13.788238   | 0            |          |
| 51  | FULLY_CONNECTED    | 13.103168   | 0.3028338    |          |
| 52  | RESHAPE            | 13.103168   | 0            |          |
| 53  | ADD                | 13.229318   | 0.2886953    |          |
| 54  | ADD                | 15.80188    | 0.288787     |          |
| 55  | FILL               | 1           | 0            |          |
| 56  | FILL               | 2E-06       | 0            |          |
| 57  | RESHAPE            | 15.80188    | 0            |          |
| 58  | TRANSPOSE          | 15.80188    | 0            |          |
| 59  | MEAN               | 0.345499    | 0.4923606    |          |
| 60  | SQUARED_DIFFERENCE | 63.224075   | 0.2779759    |          |
| 61  | MEAN               | 4.931316    | 0.3027504    |          |
| 62  | ADD                | 4.932316    | 0.0311987    |          |
| 63  | RSQRT              | 1.195838    | 0.304619     |          |
| 64  | MUL                | 1.195838    | 0            |          |
| 65  | MUL                | 10.555507   | 0.2823485    |          |
| 66  | MUL                | 0.219467    | 0.4081438    |          |
| 67  | SUB                | 0.219467    | 2.18255E-06  |          |
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
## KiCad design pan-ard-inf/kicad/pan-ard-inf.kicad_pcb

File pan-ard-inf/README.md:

# Electrical panel to Arduino hardware interface

This folder contains material related to the interface between the electrical panel and the Arduino hardware interface. See main README for a general overview and below for additional details.

## Design Considerations
[OpenEnergyMonitor](https://openenergymonitor.org/) in general was a great resource for this project and in particular the information found in [How to build an Arduino energy monitor - measuring mains voltage and current](https://learn.openenergymonitor.org/electricity-monitoring/ctac) was used to guide the design of this interface and the analog signal conditioning circuitry.

The current sensing circuitry includes a variable gain stage that is controlled by an automatic gain loop running on the Arduino. This improves signal-to-noise through the analog-to-digital conversion and improves downstream machine learning and training performance.

This subsystem was calibrated with an external power meter, yielding parameters which are used in the Arduino code that extracts the metrics used in downstream processing.

## Schematic

## PCB

## References

1. [Atmel ATmega640/V-1280/V-1281/V-2560/V-2561/V Datasheet](https://ww1.microchip.com/downloads/en/devicedoc/atmel-2549-8-bit-avr-microcontroller-atmega640-1280-1281-2560-2561_datasheet.pdf)
2. [Arduino MEGA 2560 Documentation](https://store-usa.arduino.cc/products/arduino-mega-2560-rev3?selectedStore=us)
3. [Atmel AVR465: Single-Phase Power/Energy Meter with Tamper Detection](https://ww1.microchip.com/downloads/en/Appnotes/Atmel-2566-Single-Phase-Power-Energy-Meter-with-Tamper-Detection_Ap-Notes_AVR465.pdf)

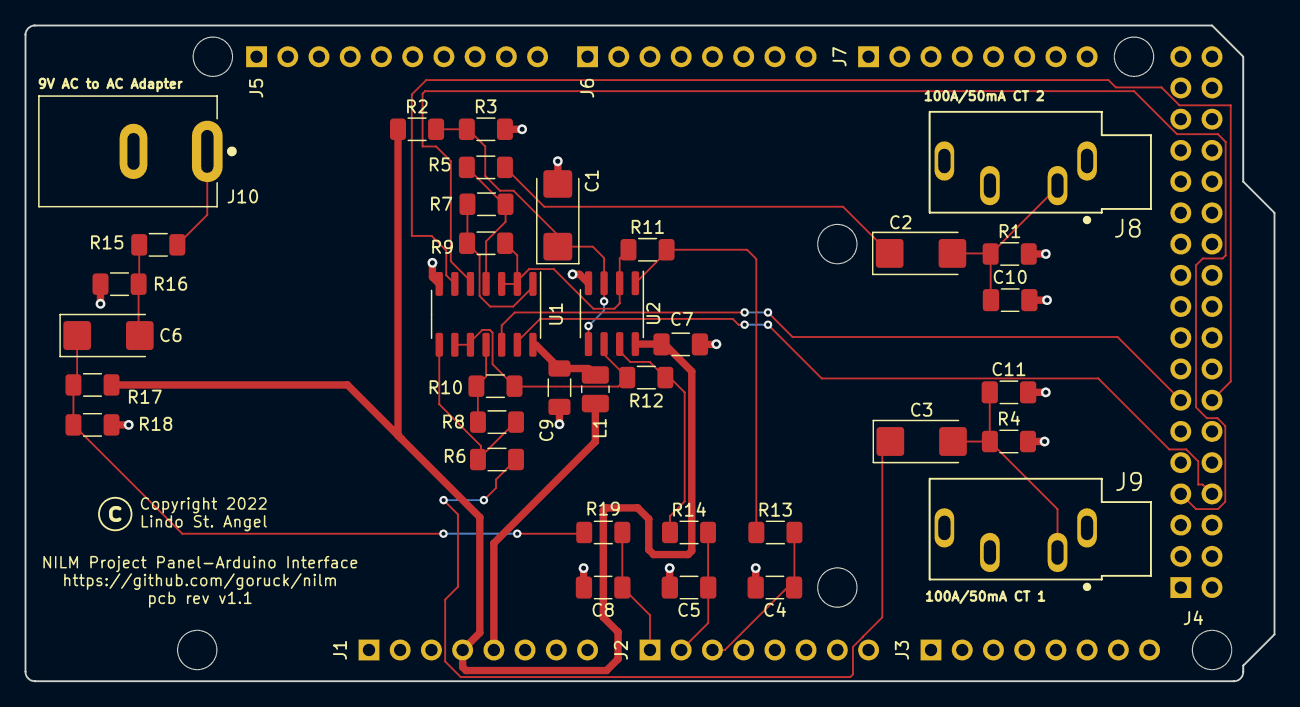
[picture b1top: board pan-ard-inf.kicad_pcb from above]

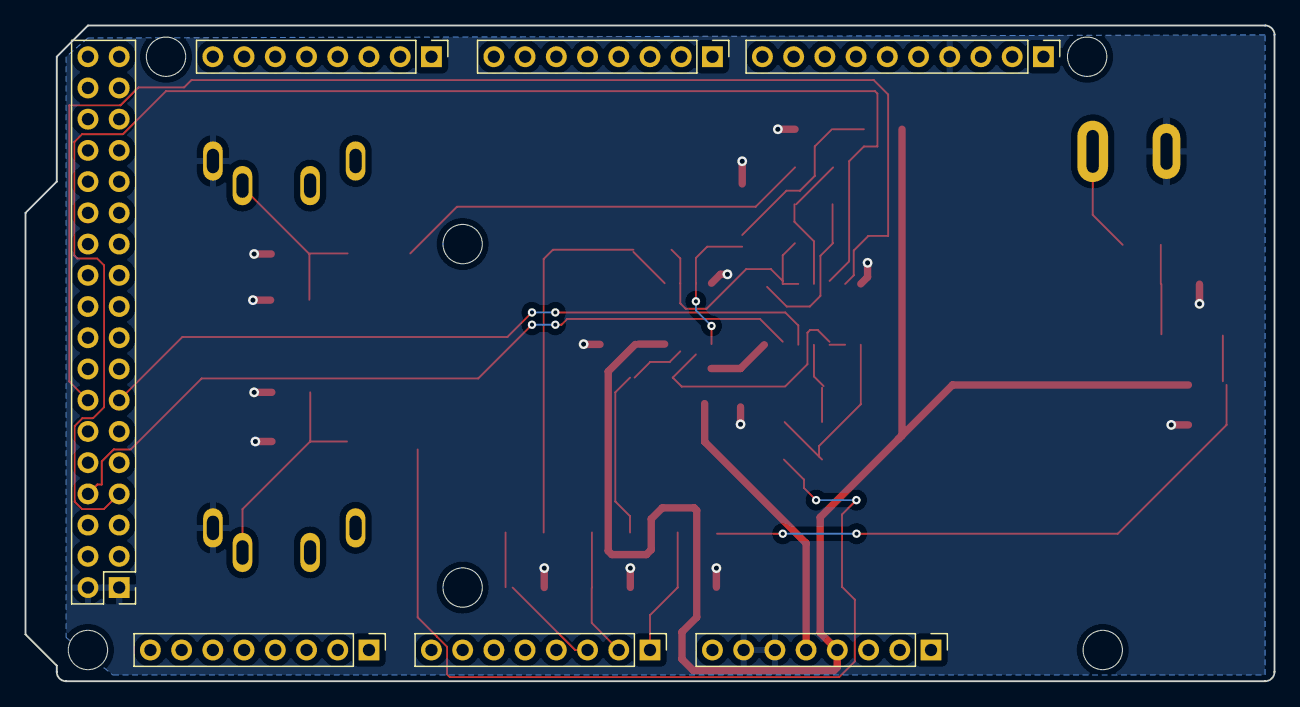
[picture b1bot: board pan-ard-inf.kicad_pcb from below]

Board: 2 copper layers, 101.6 x 53.3 mm, 49 parts (7 on the bottom side), 29 nets.

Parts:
C1: 10uF; CP_EIA-6032-20_AVX-F_Pad2.25x2.35mm_HandSolder
C2, C3, C6: 47uF; CP_EIA-6032-20_AVX-F_Pad2.25x2.35mm_HandSolder
C4, C5, C8: 0.01uF; C_1206_3216Metric_Pad1.33x1.80mm_HandSolder
C7, C9, C10, C11: 0.1uF; C_1206_3216Metric_Pad1.33x1.80mm_HandSolder
J1: Power; PinHeader_1x08_P2.54mm_Vertical
J2: Analog; PinHeader_1x08_P2.54mm_Vertical
J3: type="I" model="Analog" lib=""; PinHeader_1x08_P2.54mm_Vertical
J4: Digital; PinHeader_2x18_P2.54mm_Vertical
J5: PWM; PinHeader_1x10_P2.54mm_Vertical
J6: PWM; PinHeader_1x08_P2.54mm_Vertical
J7: Communication; PinHeader_1x08_P2.54mm_Vertical
J8, J9: SJ1-3534N; CUI_SJ1-3534N
J10: PJ-037B; CUI_PJ-037B
L1: 10uH; L_1008_2520Metric_Pad1.43x2.20mm_HandSolder
MH1, MH2, MH3, MH4, MH5, MH6: MountingHole_3.2mm
R1, R4: 14; R_1206_3216Metric_Pad1.30x1.75mm_HandSolder
R2: 1M; R_1206_3216Metric_Pad1.30x1.75mm_HandSolder
R3: 634k; R_1206_3216Metric_Pad1.30x1.75mm_HandSolder
R5, R6, R13, R14, R15, R18, R19: 7.5k; R_1206_3216Metric_Pad1.30x1.75mm_HandSolder
R7, R8: 39.2k; R_1206_3216Metric_Pad1.30x1.75mm_HandSolder
R9, R10: 332k; R_1206_3216Metric_Pad1.30x1.75mm_HandSolder
R11, R12: 475k; R_1206_3216Metric_Pad1.30x1.75mm_HandSolder
R16: 523; R_1206_3216Metric_Pad1.30x1.75mm_HandSolder
R17: 11.8k; R_1206_3216Metric_Pad1.30x1.75mm_HandSolder
U1: CD4066B; SOIC-14_3.9x8.7mm_P1.27mm
U2: LMC6482; SOIC-8_3.9x4.9mm_P1.27mm

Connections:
+3V3: C7.1, J1.4, R2.1, R17.1, U2.8 (V+)
+5V: J1.5, J4.35, J4.36, L1.1
/42: J4.13, U1.12
/43: J4.14, U1.6
/48: J4.7, U1.5
/49: J4.8, U1.13
/A0: C8.1, J2.1, R19.2
/A1: C5.1, J2.2, R14.2
/A2: C4.1, J2.3, R13.2
/P1: C3.2, C11.1, J9.2, R4.1
/P2: C2.2, C10.1, J8.2, R1.1
/SCL/21: J5.1, J7.8
/SDA/20: J5.2, J7.7
/VAC: J10.1, R15.1
GND: C1.2, C4.2, C5.2, C7.2, C8.2, C9.2, C10.2, C11.2, J1.6, J1.7, J4.1, J4.2, J5.4, J8.1, J9.1, J10.2, R1.2, R3.2, R4.2, R16.2, R18.2, U1.7 (VSS), U2.4 (V-)
unnamed: C2.1, R5.1
unnamed: C3.1, R6.2
unnamed: C6.1, R17.2, R18.1, R19.1
unnamed: C6.2, R15.2, R16.1
unnamed: R5.2, R7.1, U1.4
unnamed: R6.1, R8.2, U1.8
unnamed: R7.2, R9.1, U1.1
unnamed: R8.1, R10.1, U1.11
unnamed: R11.2, R13.1, U2.1
unnamed: R12.2, R14.1, U2.7
unnamed: C9.1, L1.2, U1.14 (VDD)
unnamed: C1.1, R2.2, R3.1, U2.3 (+), U2.5 (+)
unnamed: R9.2, R11.1, U1.2, U1.3, U2.2 (-)
unnamed: R10.2, R12.1, U1.9, U1.10, U2.6 (-)

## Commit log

2022-01-30 inital commits
2022-01-31 add mit license
2022-02-14 init commit of serial comms test
2022-02-14 first real version using EmonLibCM
2022-02-19 change ADC ref to 2.56V and add datalog interval
2022-02-20 changes for logging
2022-02-25 inital commit based off test-serial-ard.py
2022-02-25 changes to increase serial read speed
2022-04-03 inital commit
2022-04-03 change to store samples on usb hard drive
2022-04-03 change sample time
2022-04-03 init commit
2022-04-03 updated samples
2022-04-04 correct type hint
2022-04-04 add prediction results
2022-04-04 add progress bar fn to get auduino data
2022-04-06 modified predict to run inference on all appliances
2022-04-07 added metrics and thresholding, some code cleanup
2022-04-07 covered 1 day sample case
2022-04-07 updated results
2022-04-07 clarified comment
2022-04-08 code cleanup
2022-04-11 rm variable dense layer train option
2022-04-11 change to keras sequential api
2022-04-11 modify .gitignore
2022-04-15 many changes; first working version
2022-04-16 change to standard metrics + code clean up
2022-04-17 move de-norm outside infer() for better reuse
2022-04-17 add another dense layer to model for better accuracy
2022-04-19 use model i/o quant info for float <-> int8 conversion
2022-04-19 add find_test_filename()
2022-04-19 add qat option
2022-04-19 update training
2022-04-19 update test results
2022-04-19 inital version
2022-04-19 import path fixes
2022-04-19 import path fix
2022-04-20 move WindowGenerator to avoid Keras subclass
2022-04-20 move functions from common to here to avoid dependencies
2022-04-20 correct path to dataset
2022-04-20 corrected default path
2022-04-20 add pandas import
2022-04-20 fix tflite interp typo
2022-04-21 latest changes
2022-04-25 normalize data before inference + code cleanup
2022-04-28 add plotting of real-time predictions
2022-04-29 optimize real-time data plotting
2022-05-02 model optimizations for better accuracy and smaller size
2022-05-08 lower complexity of model to reduce overfitting and improve latency
2022-05-12 add thresholding to real-time predictions
2022-05-12 mainly format fixes
2022-05-12 updated training results
2022-05-29 init commit based on quantized.py
2022-05-29 init commit based on cnn_model.py
2022-05-29 deprecated
2022-05-29 add prune fine tuning; clean up code
2022-05-30 add fn to independently normalize datasets
2022-05-30 updated gitignore
2022-05-30 add add'l dataset statistical modules
2022-05-30 add thresholding; code cleanup and comment
2022-05-30 increase sample size to 5 days
2022-06-05 changes for training Keras functional models
2022-06-05 changes for models created by Keras functional api
2022-06-05 convert models to use Keras functional api
2022-06-07 make WindowGenerator a conditional keras sequence subclass
2022-06-07 update training results
2022-06-08 make tflite_infer a common function
2022-06-08 make default logger print
2022-06-08 use common functions
2022-06-08 create init file
2022-06-09 add normalization function
2022-06-09 comment edits
2022-06-09 rm unneeded import
2022-06-09 use common window generator; code clean-up
2022-06-09 mv normalization to common
2022-06-10 use common; code clean-up
2022-06-28 move expand dimensions
2022-06-28 fix typos
2022-07-04 added img folder for README.md content
2022-07-04 updated REDAME.md
2022-07-04 updated README.md for sub folders
2022-07-04 change image names to fix broken links
2022-07-05 rm old image files
2022-07-06 fix typos in README.md
2022-07-07 move image files from results to images folder
2022-10-09 added automatic gain control of analog front end
2022-10-09 added V1.1 hardware info
2022-10-10 use inline fn instead of macros & update comments
2022-10-11 fixed typo in agc call
2022-10-13 added kicad files
2022-10-13 added analog front end pcb layout image
2022-10-18 add assumed Vrms
2022-10-18 use real power instead of apparent
2023-02-01 implement new dataset scaling approach
2023-02-03 use most recent data normalization method
2023-02-04 use new normalization and UTC timestamp
2023-02-04 use updated normalization keys
2023-02-20 add transformer model
2023-03-15 latest version of model
2023-03-15 make WindowGenerator more flexible
2023-03-19 fix window center index calculation
2023-05-01 pretty much complete rewrite
2023-05-01 remove old working transformer model files
2023-05-01 add alt standardization
2023-05-01 added comments
2023-05-17 add MLM training and model updates to improve accuracy
2023-06-16 latest work in progress
2023-07-06 latest baseline
2023-07-29 add distributed training capablities
2023-08-28 updated README.md images
2023-09-20 improve logging
2023-09-20 improve comments
2023-11-15 added README.md images
2023-11-16 add transformer block visualization
2023-11-19 updated kicad files
2023-11-20 match main transformer model
2023-11-20 updated mircowave results
2023-12-01 added get_epd as static method and get_statistics as private method in NILMTestMetrics Class
2023-12-02 add saving of history as numpy array
2023-12-02 provide seperate training history save file path
2023-12-04 clean-up to remove pylint warnings
2023-12-05 window_generator no longer subclass of Keras sequence
2023-12-05 updates for most recent baseline
2023-12-05 use tf.data.Dataset for model.predict
2023-12-08 latest baseline of quantization code
2023-12-08 allow tflite interpreter to use multiple threads; logging name chnange
2023-12-10 added convert_only quant mode
2023-12-11 make fix method more flexible for selective quantization
2023-12-11 add use_fixed_model command line arg
2023-12-12 fix endless dataset generation bug
2023-12-14 fix enumerates in gen functions causing strange tf.data.Dataset issues
2023-12-21 updated .gitignore
2023-12-21 added logs
2023-12-21 added profiling and debug .csv files
2023-12-21 added .gitignore
2023-12-21 added profiling .csvs
2024-01-08 update to lastest baseline
2024-01-08 add edgetpu delegate
2024-01-08 remove unneeded command line arg
2024-01-08 add tpu model eval log
2024-01-08 fixed MCC eq.
2024-01-12 updated to latest baseline
2024-01-12 add setting of lowest-severity log msg + clean up
2024-01-12 fix typo
2024-01-12 set logger default to info
2024-01-14 use lowest_level in Logger
2024-01-14 update comments
2024-02-02 add log_file_name to Logger instance creation
2024-02-10 add ground truth
2024-02-12 use datetime indexing, general clean-up
2024-02-16 improve error handling
2024-02-16 code clean up
2024-02-25 add multiple dataset support
2024-02-26 Cover case where there is no ground truth for some appliances
2024-02-28 fix subset of appliances not working
2024-03-01 ensure correct appliance order in calculations
2024-03-13 improve ground truth data processing and cleanup
2024-03-17 Remove NaNs from metric calcs + cleanup
2024-03-28 initial version
2024-03-29 log total number of samples
2024-03-29 make dataset naming consistant w/convention
2024-04-04 inital version of model fine tuning.
2024-04-04 make model definition a callable in init
2024-04-04 update for latest DistributedTrainer class
2024-04-04 update comments in params_appliance
2024-04-06 lower kettle on power threshold
2024-04-15 clarify fine_tune_model function
2024-04-15 add cnn_fine_tune as model arch
2024-04-16 only generate train and val datasets
2024-04-17 make model_arch cmd line arg default a list
2024-04-19 add filtering of datasets based on not_before arg
2024-04-20 fix not_before logic
2024-04-21 add error checking for not_before arg
2024-04-21 update fine tuned model
2024-04-29 log agc state;use assumed mains rms voltag correctly
2024-04-29 update for logging of agc status and assumed Vrms flag
2024-04-29 add .vscode config files
2024-04-29 add .vscode settings config
2024-04-29 adding back .vscode settings
2024-04-30 code clean up; clarify AC present flag
2024-04-30 clarify AC present flag
2024-04-30 fix ac present comment
2024-05-10 add .env to set PYTHONPATH for imports
2024-05-10 add nilm.code-workspace config
2024-05-10 rm old log files
2024-05-10 rm old transformer model
2024-05-10 add results folder and contents
2024-05-10 update image folder contents
2024-05-10 update models folder content
2024-05-10 update dataset management log files
2024-05-10 make default appliance washingmachine
2024-05-19 fix import path and code clean-up
2024-05-19 update time zone zone names
2024-05-19 update logs
2024-05-19 update plot pngs
2024-05-21 fix plot misalignment & code cleanup
2024-05-21 update fine tuning results
2024-05-22 rm rpi/samples.csv
2024-05-23 fix import errors
2024-05-23 rm rpi/.gitignore
2024-05-23 update profiling results
2025-09-08 fix equations in README.md

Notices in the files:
README.md:
The REFIT dataset used in this project is is licensed under the Creative Commons Attribution 4.0 International Public License.
pan-ard-inf/kicad/pan-ard-inf.kicad_pcb:
Copyright 2022 Lindo St. Angel
